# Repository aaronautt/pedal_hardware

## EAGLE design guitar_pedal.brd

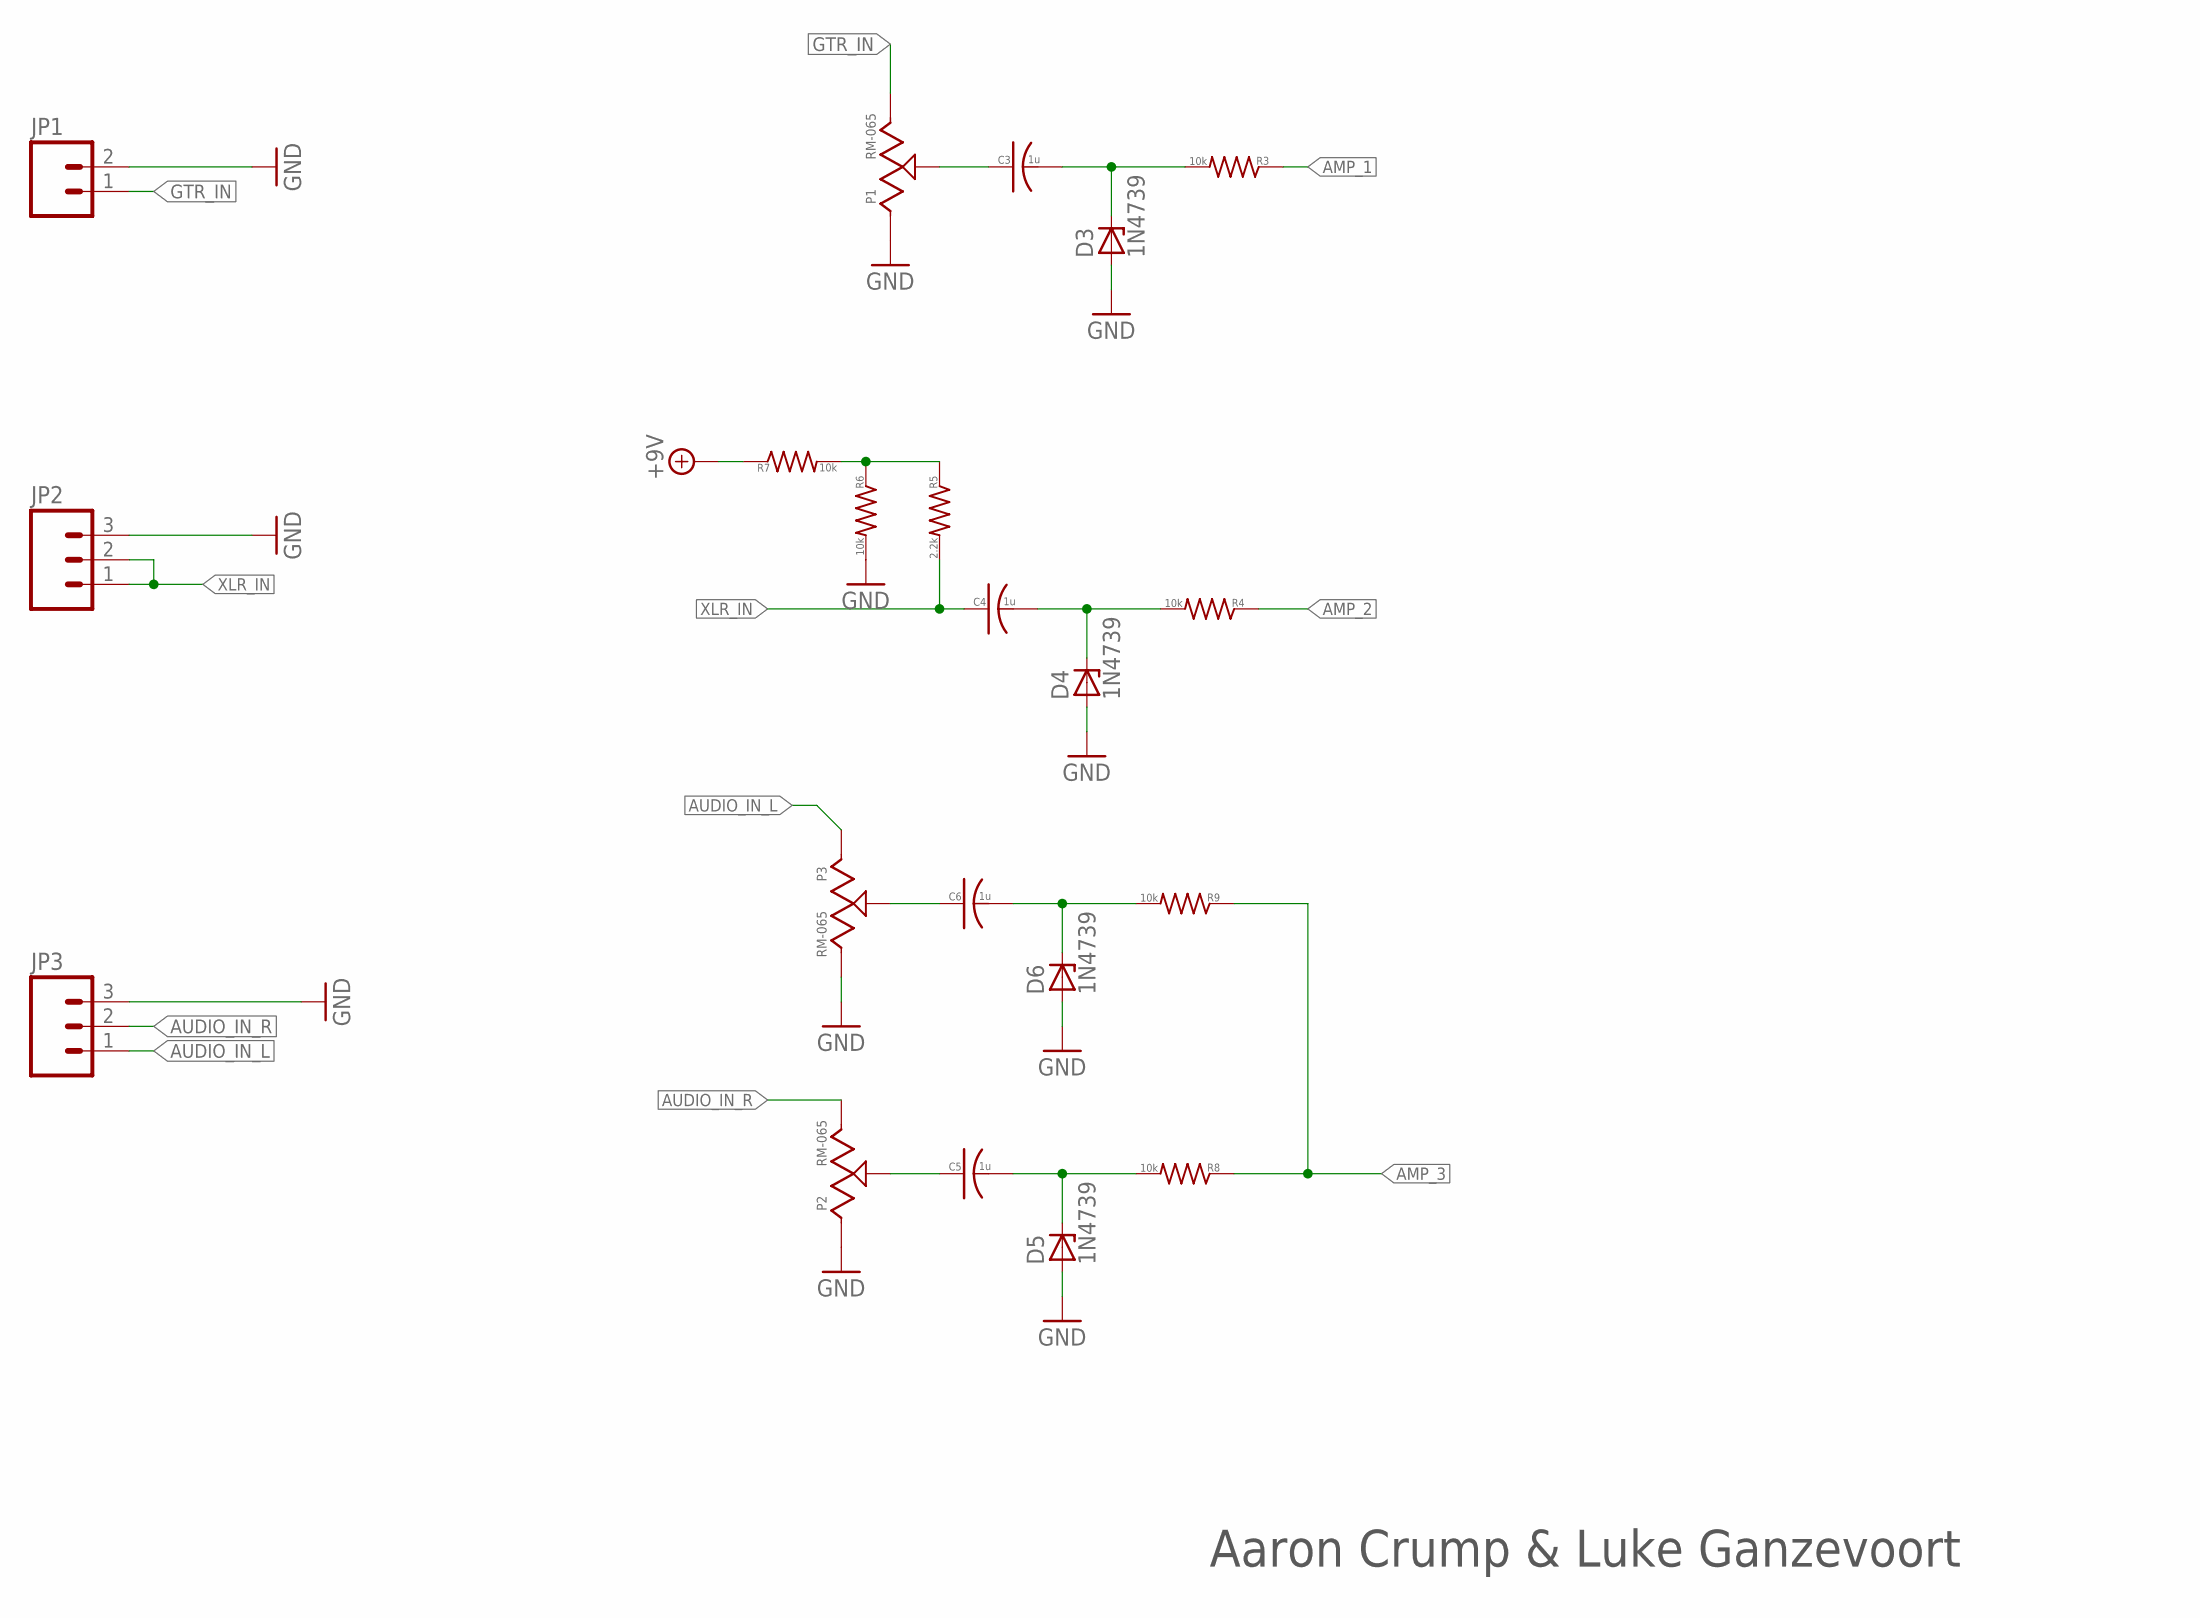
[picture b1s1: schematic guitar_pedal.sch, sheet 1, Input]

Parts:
C3, C4, C5, C6: 1u; C0805
D3, D4, D5, D6: 1N4739; DO41-7
JP1: M02PTH; 1X02
JP2, JP3: M03PTH; 1X03
P1, P2, P3: RM-065
R3, R4, R6, R7, R8, R9: 10k; C0805
R5: 2.2k; C0805

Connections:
+9V: R7.1; also elsewhere on the board
AMP_1: R3.1; also elsewhere on the board
AMP_2: R4.1; also elsewhere on the board
AMP_3: R8.1, R9.1; also elsewhere on the board
AUDIO_IN_L: JP3.1, P3.1
AUDIO_IN_R: JP3.2, P2.3 (2)
GND: D3.A, D4.A, D5.A, D6.A, JP1.2, JP2.3, JP3.3, P1.1, P2.1, P3.3 (2), R6.2; also elsewhere on the board
GTR_IN: JP1.1, P1.3 (2)
unnamed: C5.1 (POS), P2.2 (W)
unnamed: R5.1, R6.1, R7.2
unnamed: C3.1 (POS), P1.2 (W)
unnamed: C6.1 (POS), P3.2 (W)
unnamed: C4.2 (NEG), D4.C, R4.2
unnamed: C6.2 (NEG), D6.C, R9.2
unnamed: C5.2 (NEG), D5.C, R8.2
unnamed: C3.2 (NEG), D3.C, R3.2
XLR_IN: C4.1 (POS), JP2.1, JP2.2, R5.2

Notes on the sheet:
Aaron Crump & Luke Ganzevoort

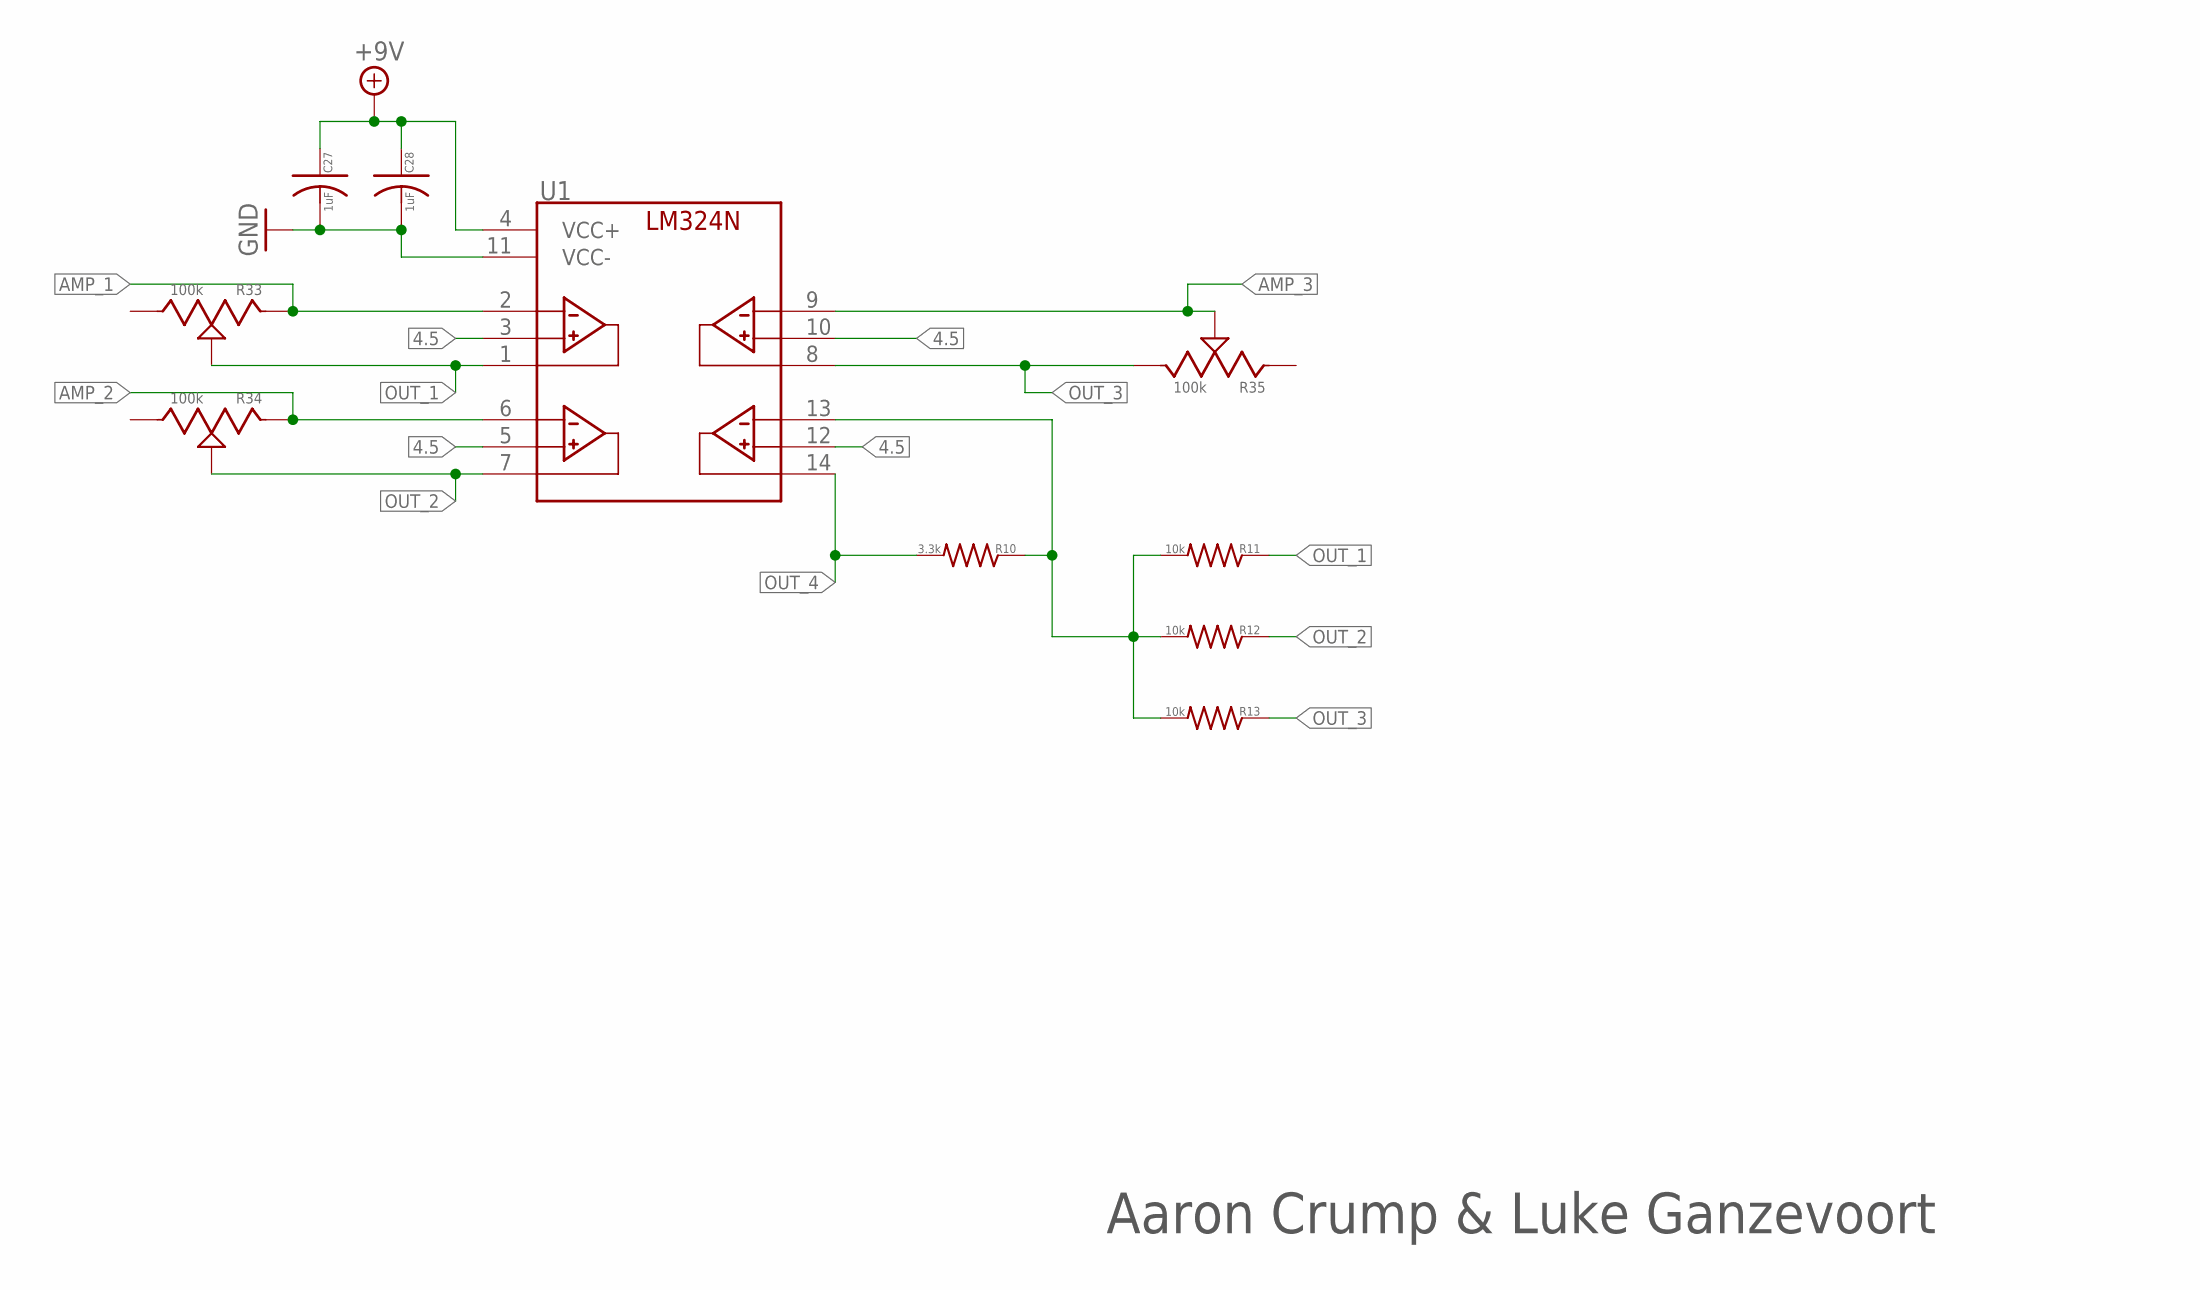
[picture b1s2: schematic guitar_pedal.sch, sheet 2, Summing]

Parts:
C27, C28: 1uF; C0805
R10: 3.3k; C0805
R11, R12, R13: 10k; C0805
R33, R34, R35: 100k; 1X03_LONGPADS
U1: LM324NSOIC-14; SOIC-14

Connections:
4.5: U1.3 (NINV_IN_1), U1.5 (NINV_IN_2), U1.10 (NINV_3), U1.12 (NINV_4); also elsewhere on the board
+9V: C27.1 (POS), C28.1 (POS), U1.4 (VCC+); also elsewhere on the board
AMP_1: R33.1, U1.2 (INV_IN_1); also elsewhere on the board
AMP_2: R34.1, U1.6 (INV_IN_2); also elsewhere on the board
AMP_3: R35.2 (W), U1.9 (INV_3); also elsewhere on the board
GND: C27.2 (NEG), C28.2 (NEG), U1.11 (VCC-); also elsewhere on the board
unnamed: R10.1, R11.2, R12.2, R13.2, U1.13 (INV_4)
OUT_1: R11.1, R33.2 (W), U1.1 (OUT_1)
OUT_2: R12.1, R34.2 (W), U1.7 (OUT_2)
OUT_3: R13.1, R35.3 (2), U1.8 (OUT_3)
OUT_4: R10.2, U1.14 (OUT_4); also elsewhere on the board

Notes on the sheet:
Aaron Crump & Luke Ganzevoort

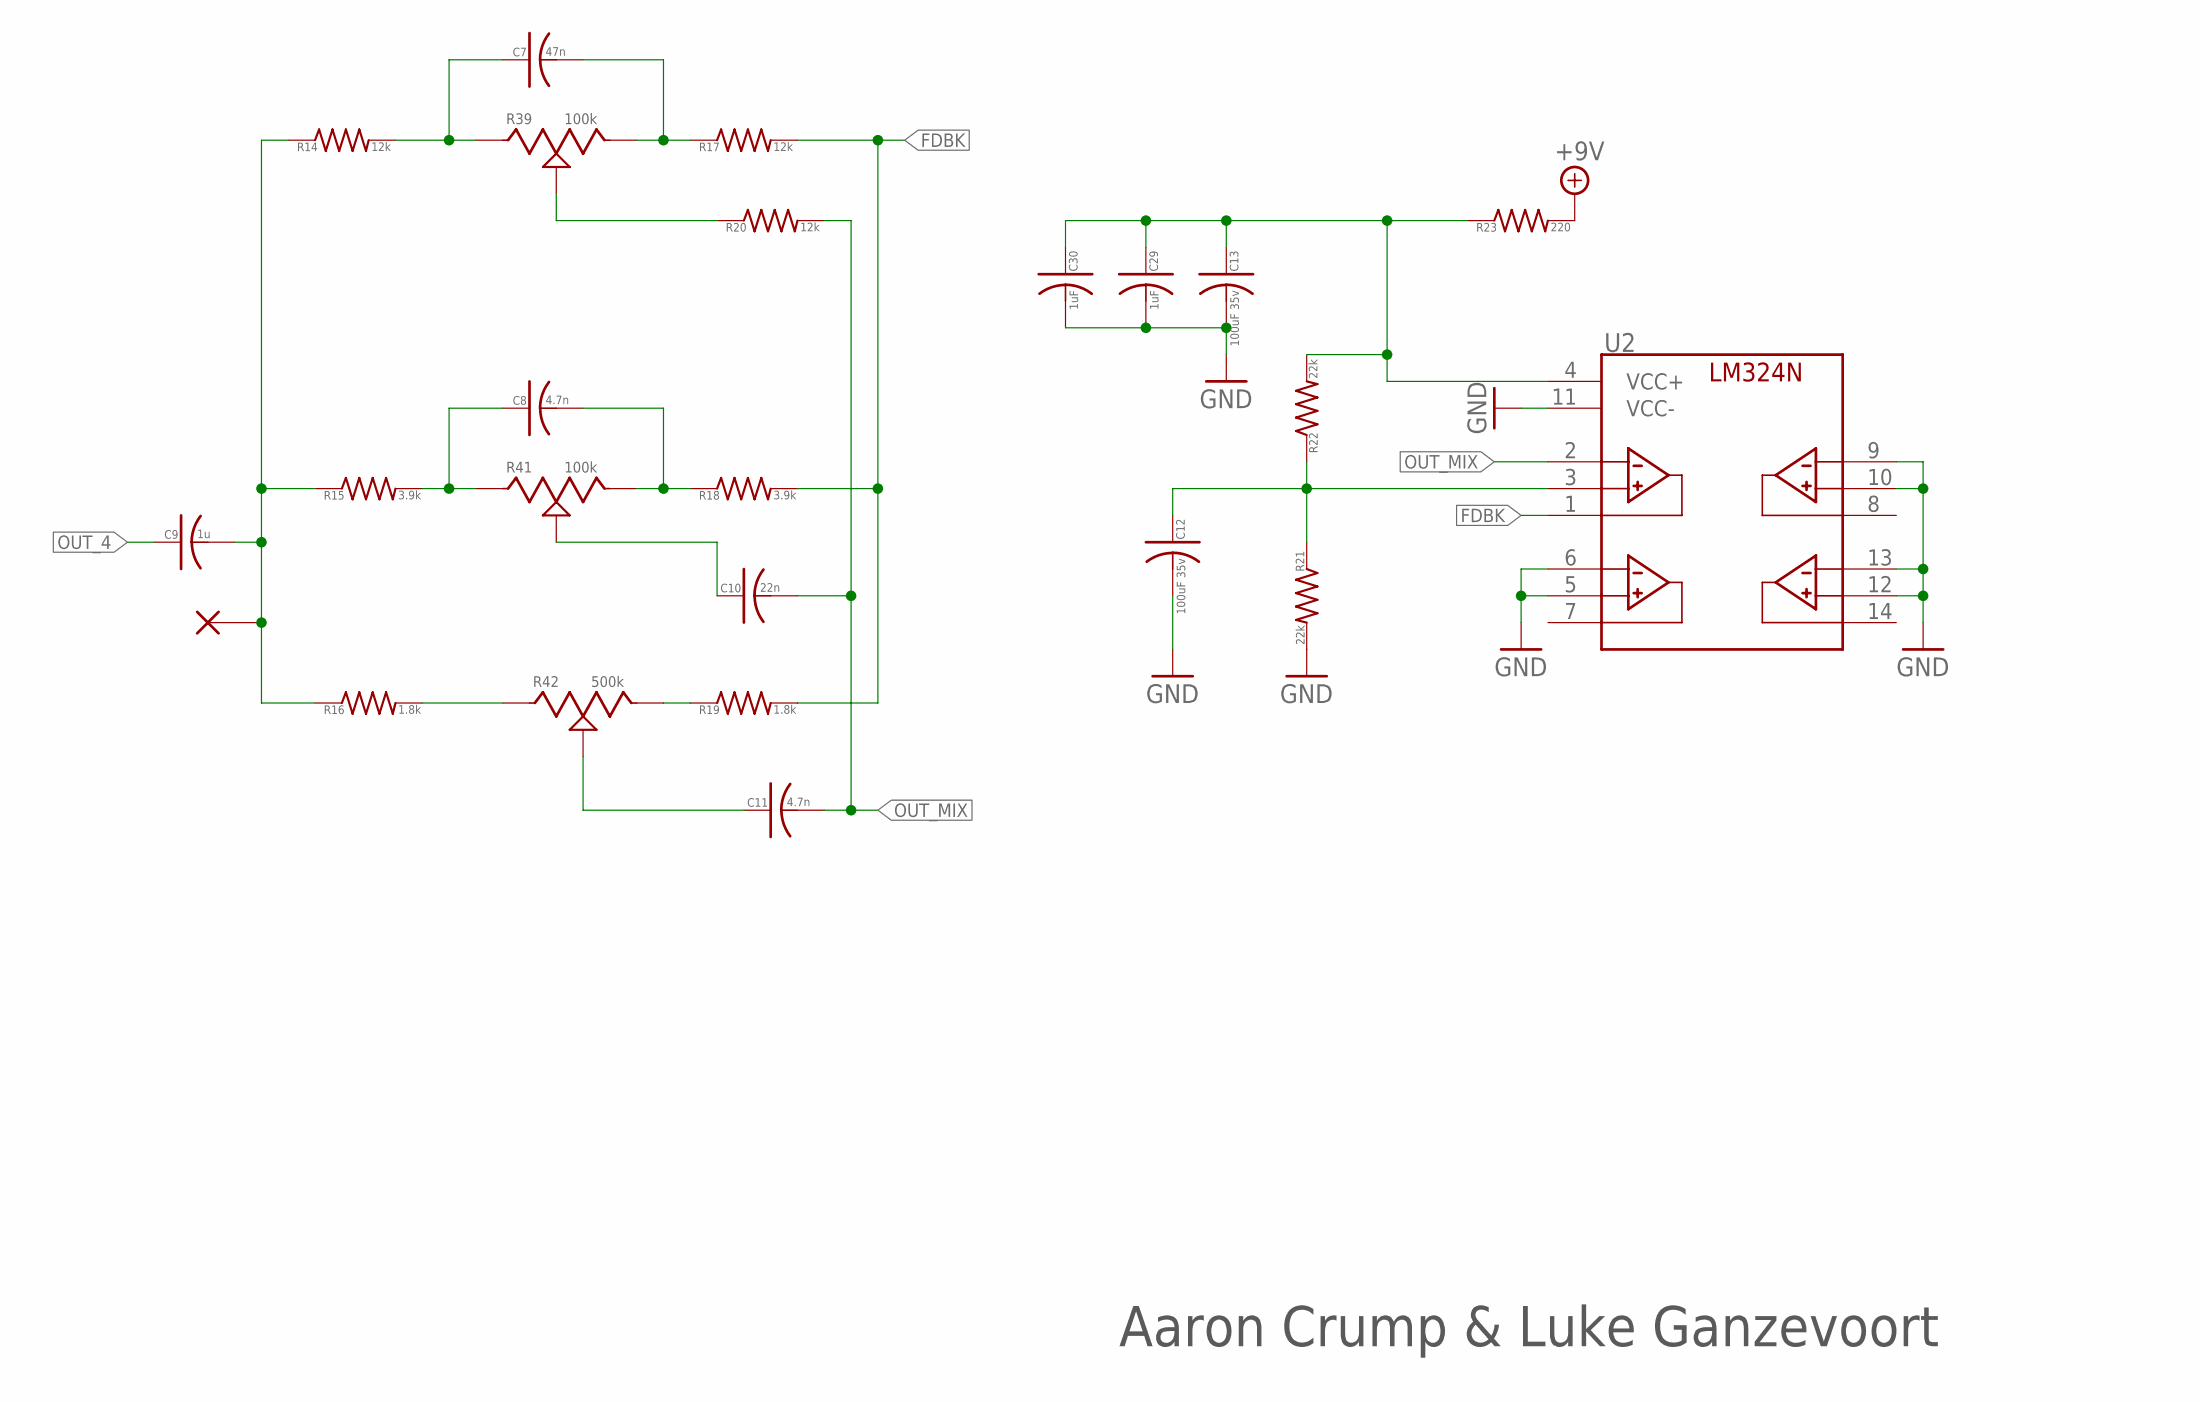
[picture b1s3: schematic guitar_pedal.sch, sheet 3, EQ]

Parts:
C7: 47n; C0805
C8, C11: 4.7n; C0805
C9: 1u; C0805
C10: 22n; C0805
C12, C13: 100uF 35v; CAN_6MM
C29, C30: 1uF; C0805
R14, R17, R20: 12k; C0805
R15, R18: 3.9k; C0805
R16, R19: 1.8k; C0805
R21, R22: 22k; C0805
R23: 220; C0805
R39, R41: 100k; 1X03_LONGPADS
R42: 500k; 1X03_LONGPADS
U2: LM324NSOIC-14; SOIC-14
V2: EQin; VIA1

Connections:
+9V: R23.2; also elsewhere on the board
FDBK: R17.2, R18.2, R19.2, U2.1 (OUT_1); also elsewhere on the board
GND: C12.P- (NEG), C13.P- (NEG), C29.2 (NEG), C30.2 (NEG), R21.2, U2.5 (NINV_IN_2), U2.6 (INV_IN_2), U2.9 (INV_3), U2.10 (NINV_3), U2.11 (VCC-), U2.12 (NINV_4), U2.13 (INV_4); also elsewhere on the board
unnamed: C13.P+ (POS), C29.1 (POS), C30.1 (POS), R22.2, R23.1, U2.4 (VCC+)
unnamed: C7.1 (POS), R14.2, R39.1
unnamed: C8.1 (POS), R15.2, R41.1
unnamed: R16.2, R42.1
unnamed: C9.2 (NEG), R14.1, R15.1, R16.1, V2.P$1
unnamed: C11.1 (POS), R42.2 (W)
unnamed: C7.2 (NEG), R17.1, R39.3 (2)
unnamed: C8.2 (NEG), R18.1, R41.3 (2)
unnamed: R19.1, R42.3 (2)
unnamed: R20.1, R39.2 (W)
unnamed: C10.1 (POS), R41.2 (W)
unnamed: C12.P+ (POS), R21.1, R22.1, U2.3 (NINV_IN_1)
OUT_4: C9.1 (POS); also elsewhere on the board
OUT_MIX: C10.2 (NEG), C11.2 (NEG), R20.2, U2.2 (INV_IN_1)

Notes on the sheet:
Aaron Crump & Luke Ganzevoort

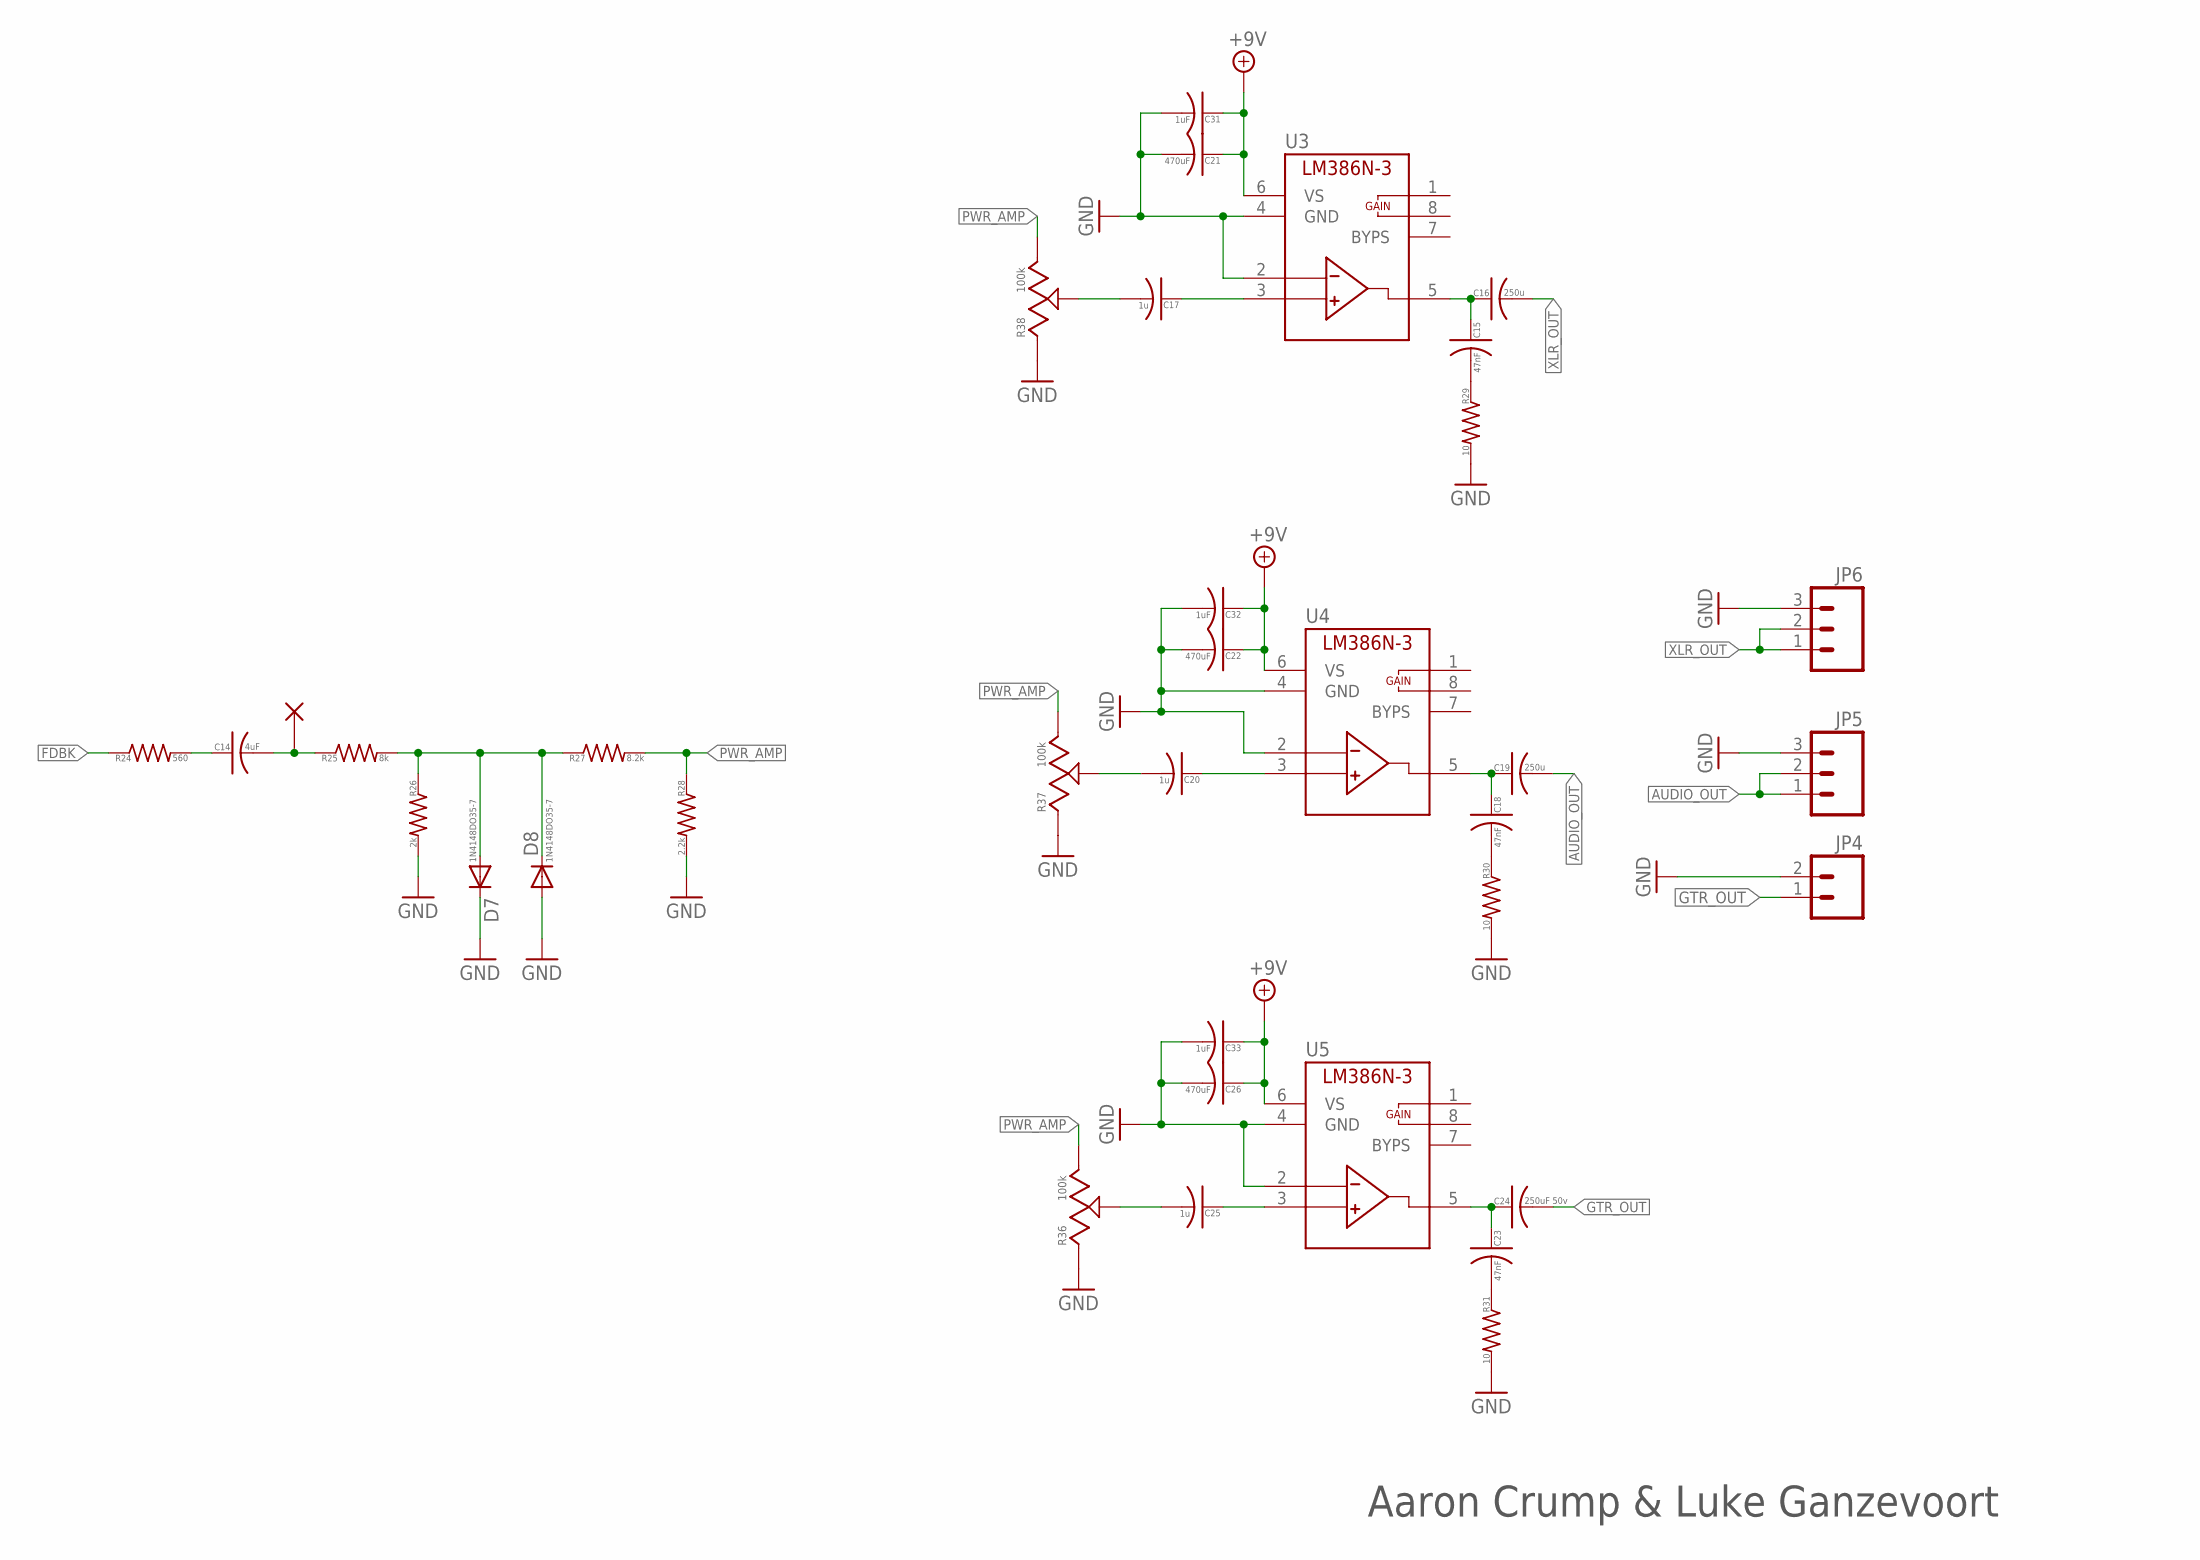
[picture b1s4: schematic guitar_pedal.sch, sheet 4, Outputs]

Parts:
C14: 4uF; C0805
C15, C18, C23: 47nF; C0805
C16, C19: 250u; CAN01
C17, C20, C25: 1u; C0805
C21, C22, C26: 470uF; CAN01
C24: 250uF 50v; CAN01
C31, C32, C33: 1uF; C0805
D7, D8: 1N4148DO35-7; DO35-7
JP4: M02PTH; 1X02
JP5, JP6: M03PTH; 1X03
R24: 560; C0805
R25: 8k; C0805
R26: 2k; C0805
R27: 8.2k; C0805
R28: 2.2k; C0805
R29, R30, R31: 10; C0805
R36, R37, R38: 100k; 1X03_LONGPADS
U3, U4, U5: LM386N-3; DIL08
V17: EQout; VIA1

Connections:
+9V: C21.+ (POS), C22.+ (POS), C26.+ (POS), C31.1 (POS), C32.1 (POS), C33.1 (POS), U3.6 (VS), U4.6 (VS), U5.6 (VS); also elsewhere on the board
AUDIO_OUT: C19.- (NEG), JP5.1, JP5.2
FDBK: R24.1; also elsewhere on the board
GND: C21.- (NEG), C22.- (NEG), C26.- (NEG), C31.2 (NEG), C32.2 (NEG), C33.2 (NEG), D7.C, D8.A, JP4.2, JP5.3, JP6.3, R26.2, R28.2, R29.2, R30.2, R31.2, R36.1, R37.1, R38.1, U3.2 (-IN), U3.4 (GND), U4.2 (-IN), U4.4 (GND), U5.2 (-IN), U5.4 (GND); also elsewhere on the board
GTR_OUT: C24.- (NEG), JP4.1
unnamed: C15.1 (POS), C16.+ (POS), U3.5 (VOUT)
unnamed: C14.1 (POS), R24.2
unnamed: C14.2 (NEG), R25.1, V17.P$1
unnamed: D7.A, D8.C, R25.2, R26.1, R27.1
unnamed: C15.2 (NEG), R29.1
unnamed: C17.2 (NEG), R38.2 (W)
unnamed: C18.1 (POS), C19.+ (POS), U4.5 (VOUT)
unnamed: C20.1 (POS), U4.3 (+IN)
unnamed: C17.1 (POS), U3.3 (+IN)
unnamed: C18.2 (NEG), R30.1
unnamed: C20.2 (NEG), R37.2 (W)
unnamed: C23.1 (POS), C24.+ (POS), U5.5 (VOUT)
unnamed: C25.1 (POS), U5.3 (+IN)
unnamed: C23.2 (NEG), R31.1
unnamed: C25.2 (NEG), R36.2 (W)
PWR_AMP: R27.2, R28.1, R36.3 (2), R37.3 (2), R38.3 (2)
XLR_OUT: C16.- (NEG), JP6.1, JP6.2

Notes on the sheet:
Aaron Crump & Luke Ganzevoort

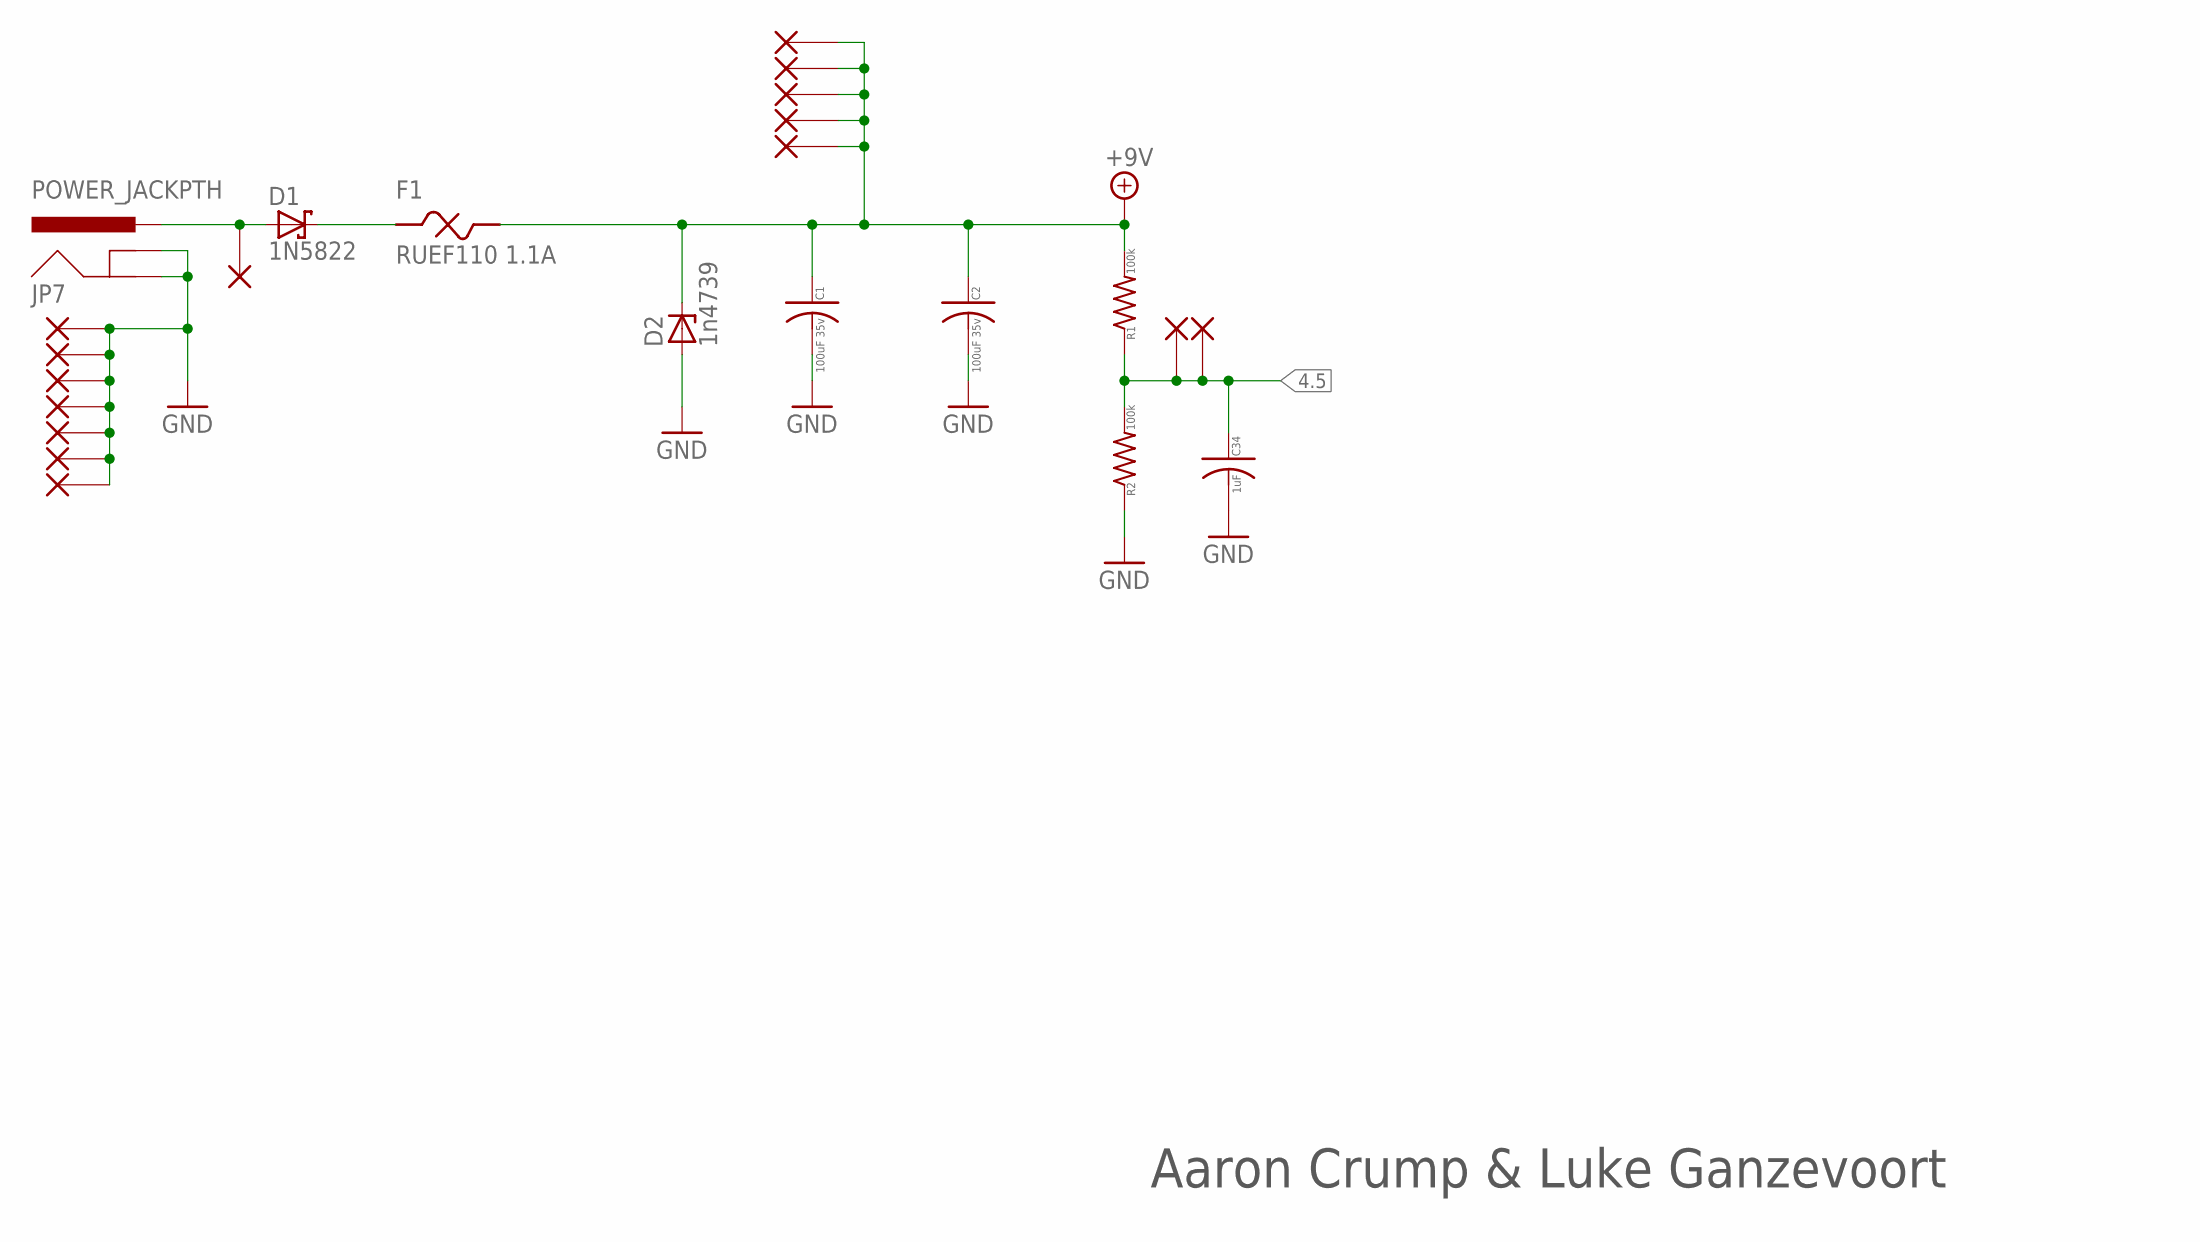
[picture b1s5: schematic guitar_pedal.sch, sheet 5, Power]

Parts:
C1, C2: 100uF 35v; CAN_6MM
C34: 1uF; C0805
D1: 1N5822; DO201T15
D2: 1n4739; DO41-7
F1: RUEF110 1.1A; RADIAL_PTC_RUEF110
JP7: POWER_JACKPTH; POWER_JACK_PTH
R1, R2: 100k; C0805
V1: V+; VIA1
V3, V4, V5, V6, V7: 9v; VIA1
V8, V9: 4v5; VIA1
V10, V11, V12, V13, V14, V15, V16: GND; VIA1

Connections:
4.5: C34.1 (POS), R1.1, R2.2, V8.P$1, V9.P$1; also elsewhere on the board
+9V: C1.P+ (POS), C2.P+ (POS), D2.C, F1.P$2 (2), R1.2, V3.P$1, V4.P$1, V5.P$1, V6.P$1, V7.P$1; also elsewhere on the board
GND: C1.P- (NEG), C2.P- (NEG), C34.2 (NEG), D2.A, JP7.GND, JP7.GNDBREAK, R2.1, V10.P$1, V11.P$1, V12.P$1, V13.P$1, V14.P$1, V15.P$1, V16.P$1; also elsewhere on the board
unnamed: D1.A, JP7.PWR, V1.P$1
unnamed: D1.C, F1.P$1 (1)

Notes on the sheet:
Aaron Crump & Luke Ganzevoort

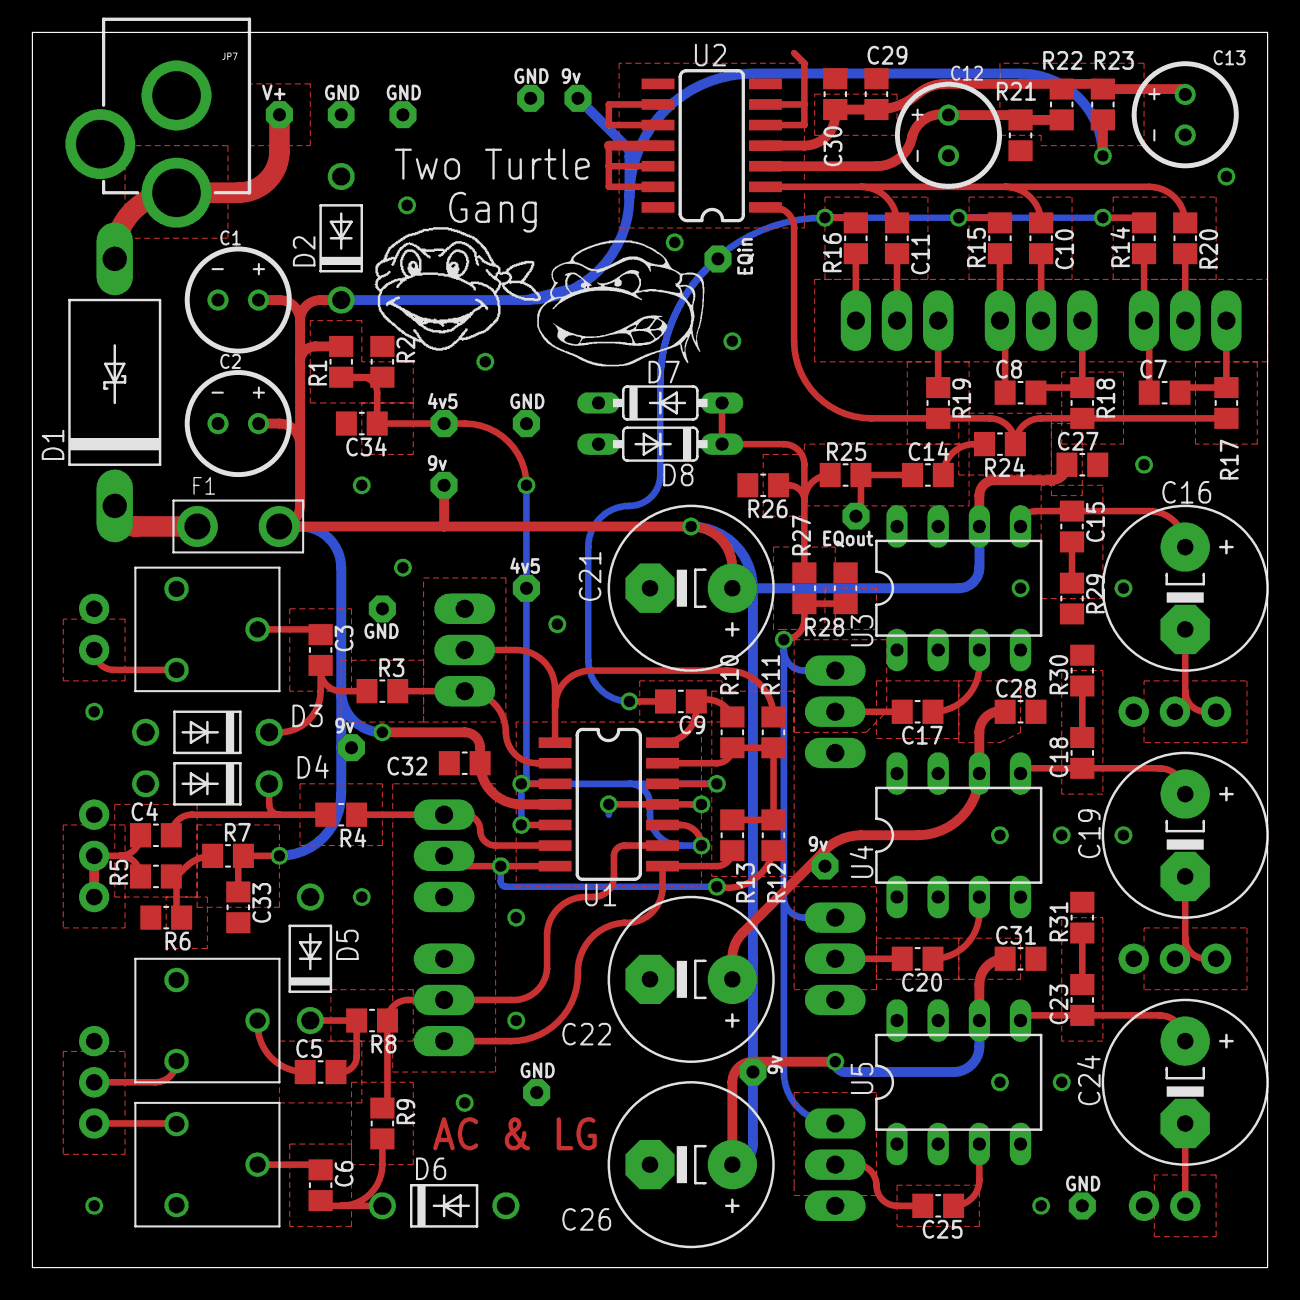
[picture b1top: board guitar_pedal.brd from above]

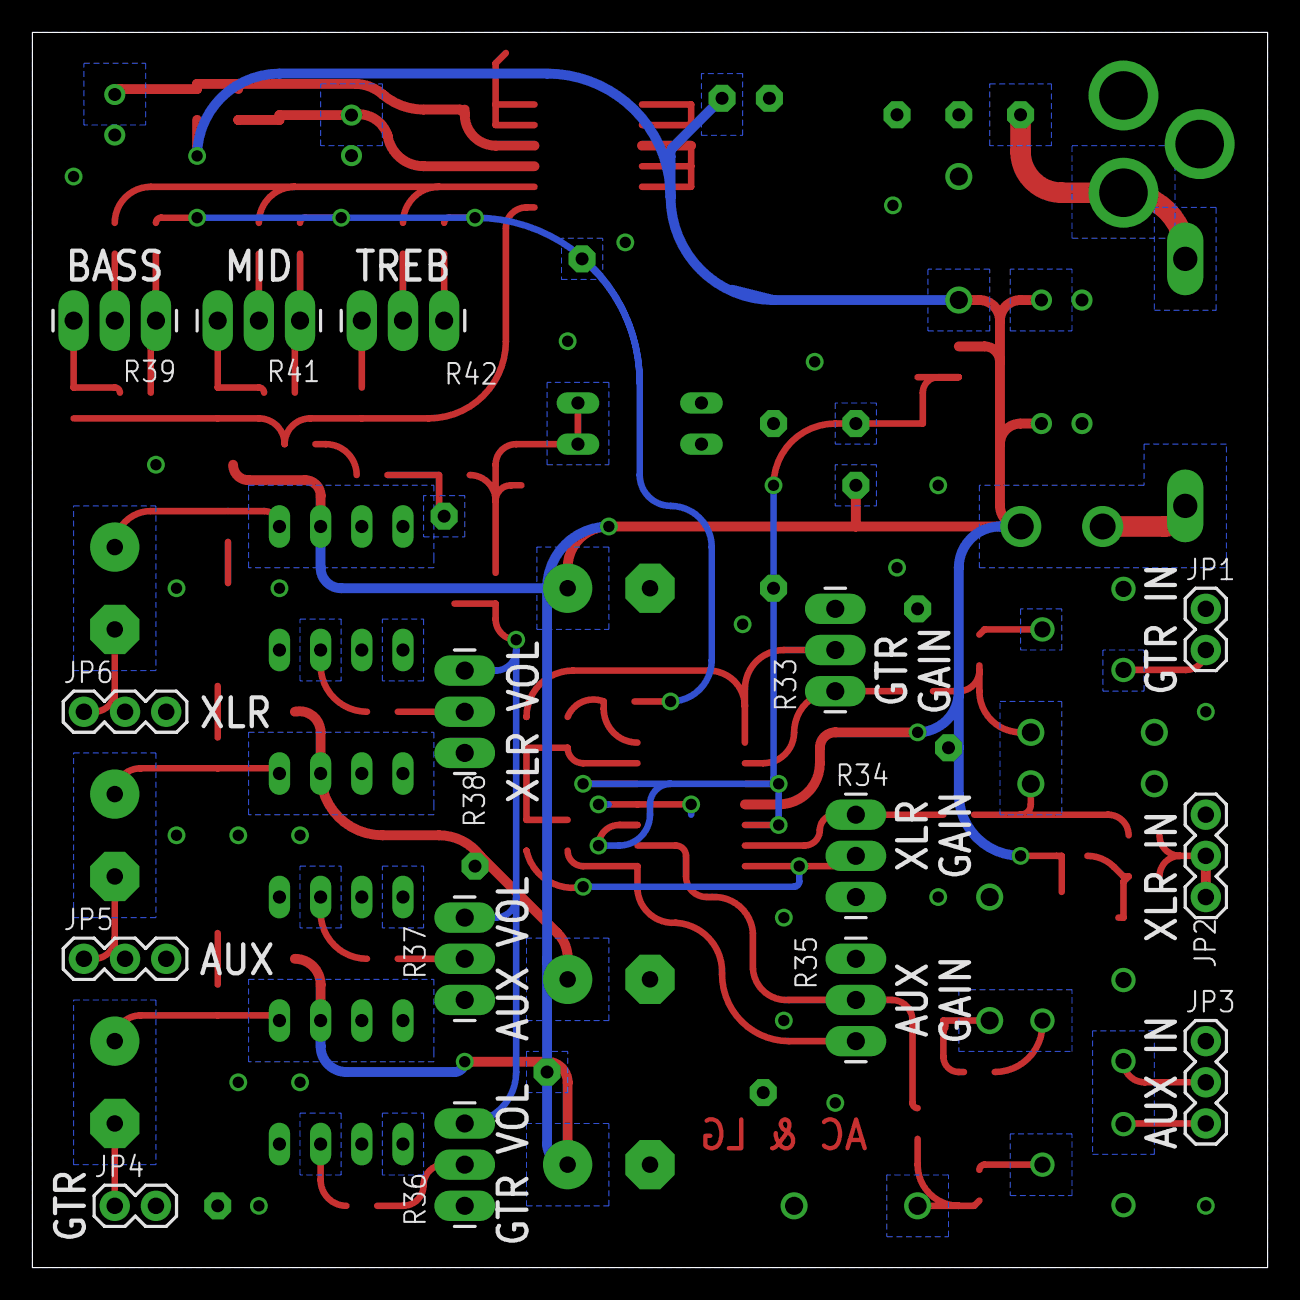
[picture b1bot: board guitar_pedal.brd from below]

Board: 2 copper layers, 76.2 x 76.2 mm, 117 parts (15 on the bottom side), 58 nets.

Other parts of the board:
U$1: NINJA_TURTLE1
U$2: NINJA_TURTLE2

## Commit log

2015-11-16 mostly finished schematic, still needs stomp switch
2015-11-16 removing backup files.
2015-11-16 added aarons library
2015-11-16 Began to organize into different sheets.
2015-11-16 Finished organizing sheets
2015-11-16 editted schematic to orgainize and fix mistakes.
2015-11-17 finished schematic changes
2015-11-17 Started layout. Placed output components.
2015-11-18 Finished laying out the components.
2015-11-19 changed PTC to tayda 1.1A through hole component.
2015-11-19 Finished layout! Still need silk screen.
2015-11-19 Added most of silk screen. Added vias for debugging. Added ground vias. Added ground plane cutout to through hole components for case with no solder mask.
2015-11-19 Finished layout.
2015-11-19 prepared to reset master
2015-11-19 Mergered back into master
2015-11-19 added

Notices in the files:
parts and their libraries:
SparkFun-Connectors: Licensing: Creative Commons ShareAlike 4.0 International - https://creativecommons.org/licenses/by-sa/4.0
